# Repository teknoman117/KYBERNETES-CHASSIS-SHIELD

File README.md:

# Kybernetes 2 Chassis Control Shield

Arduino Uno R3 shield for controlling the chassis functions of Kybernetes 2

## Functions

* Battery Protection for Motion Battery
* Isolated control of Steering Servos
* Isolated control of ESC
* Kill Switch (ATTINY85) - out of band ESC arming management, Radio PWM input
* Quadrature Encoder Input for velocity control and odometry
* Bumper Input for contact sensors
* I2C bus for current sensors, sonar, imu, etc.

## Firmware

### Assembled

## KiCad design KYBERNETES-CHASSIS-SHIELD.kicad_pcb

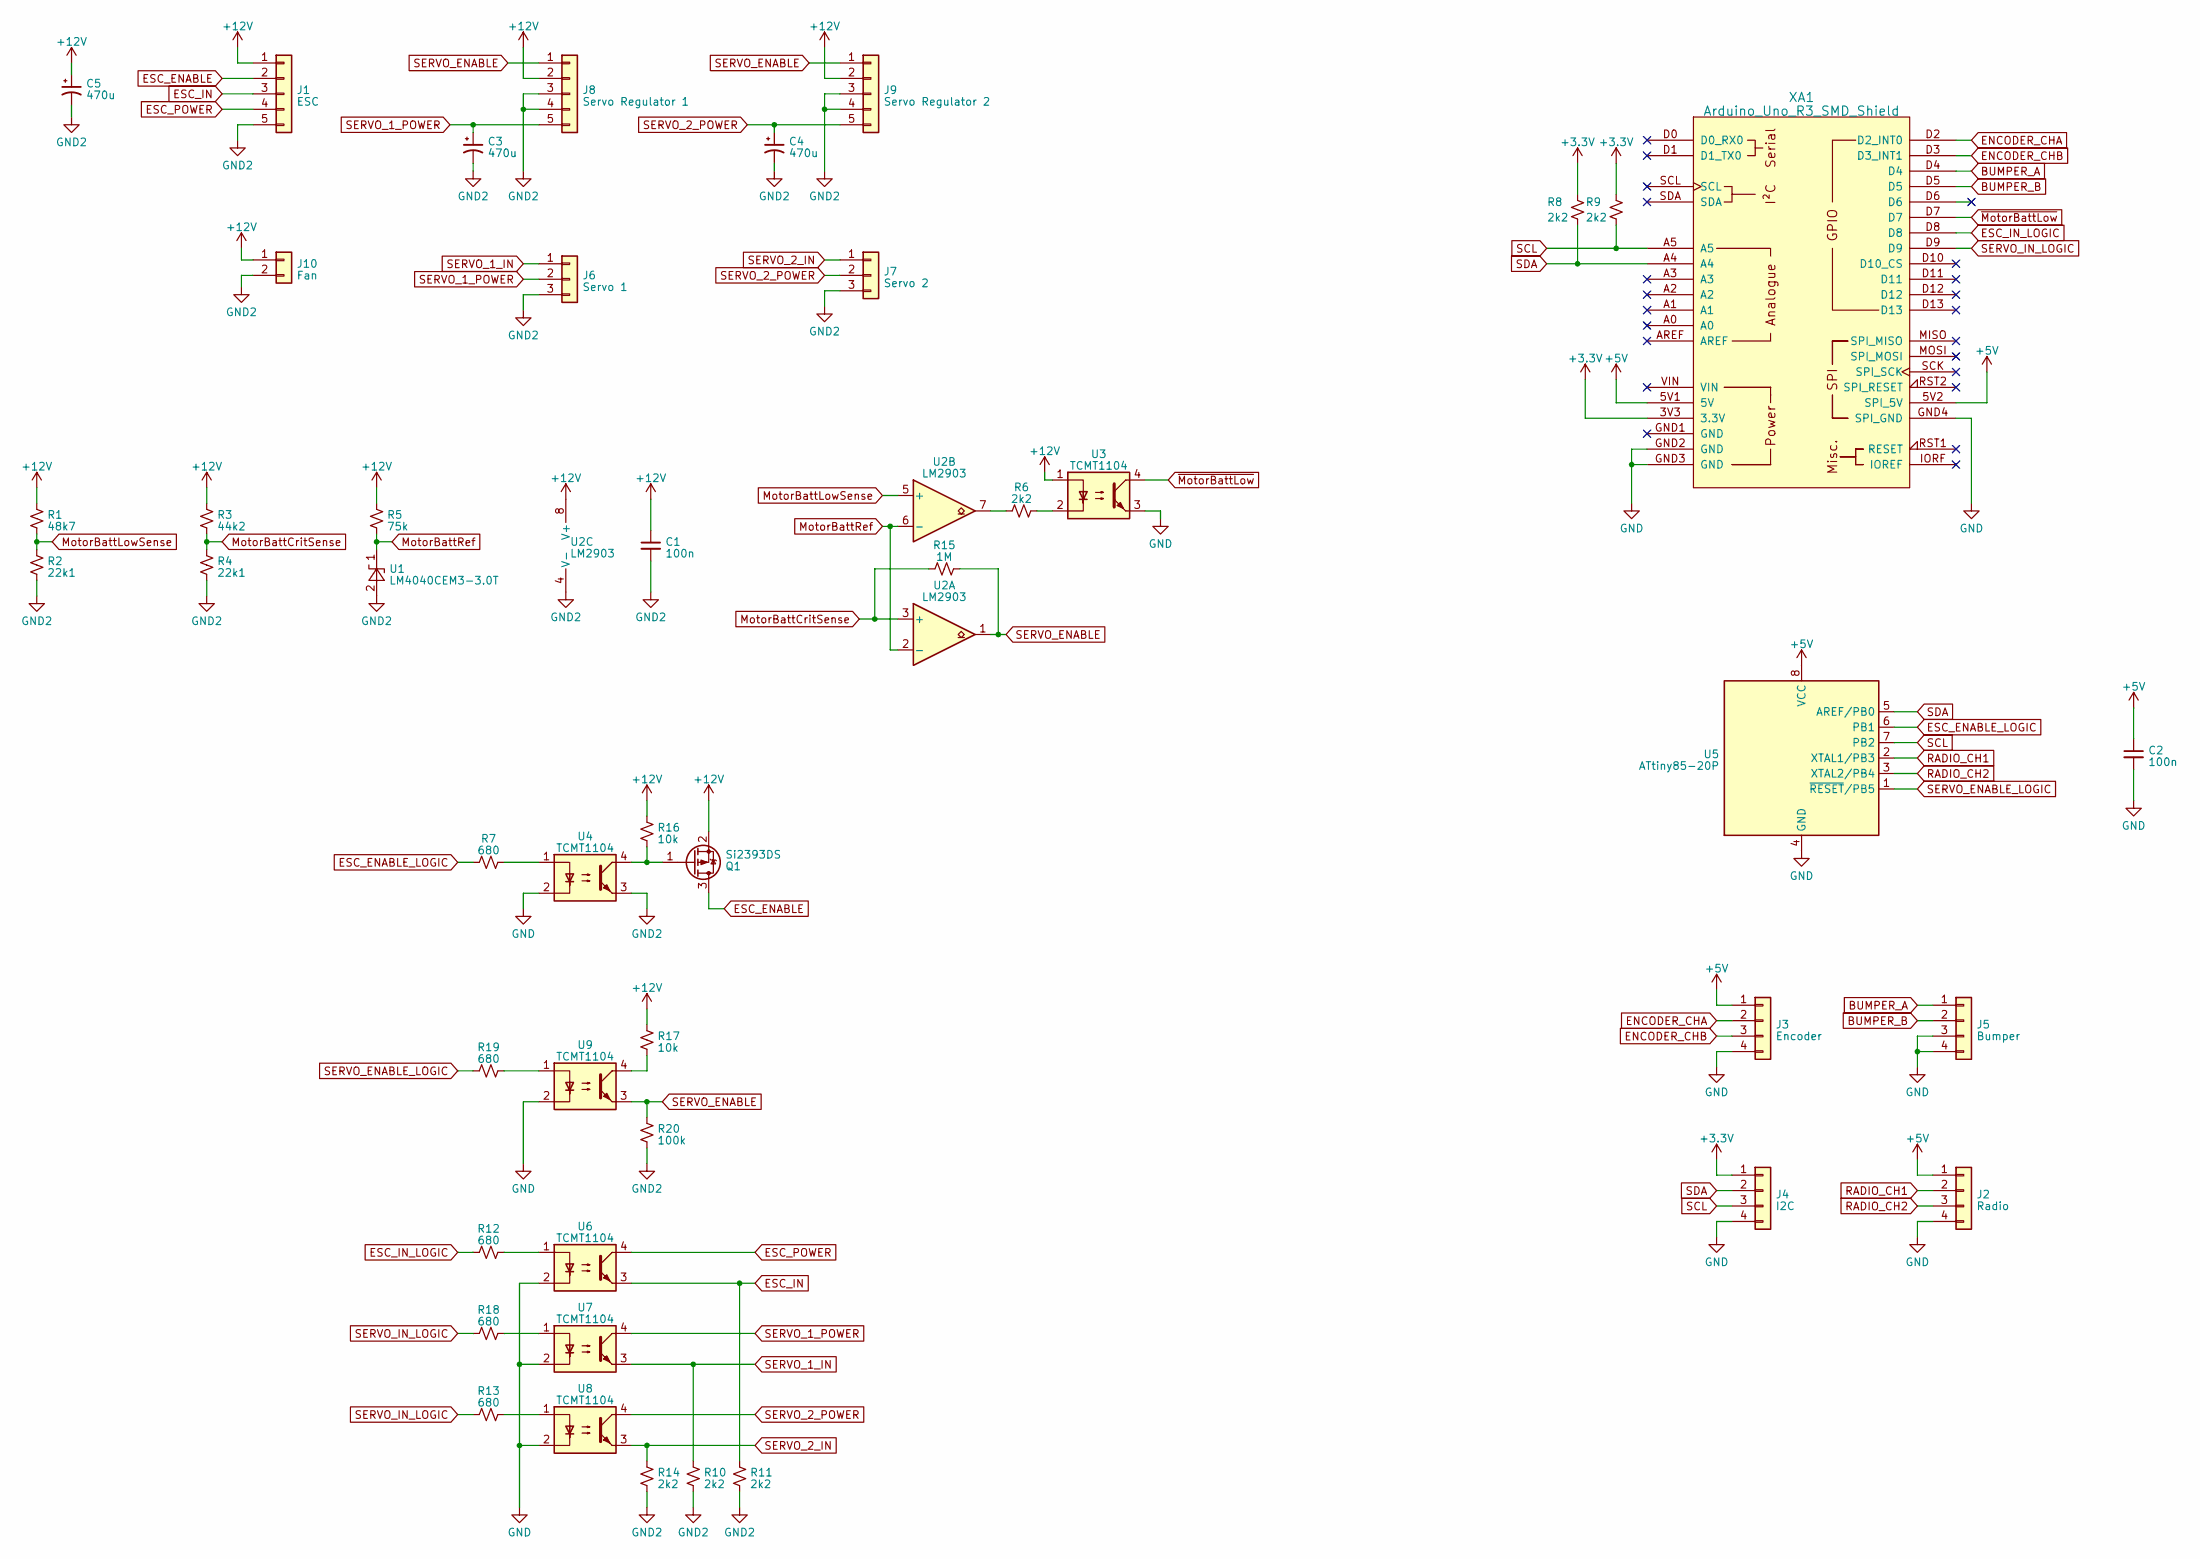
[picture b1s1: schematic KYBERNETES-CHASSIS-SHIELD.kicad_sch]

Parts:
C1, C2: 100n; C_0603_1608Metric_Pad1.08x0.95mm_HandSolder
C3, C4, C5: 470u; CP_Elec_10x10.5
J1: ESC; JST_PH_B5B-PH-K_1x05_P2.00mm_Vertical
J2: Radio; JST_PH_B4B-PH-K_1x04_P2.00mm_Vertical
J3: Encoder; JST_PH_B4B-PH-K_1x04_P2.00mm_Vertical
J4: I2C; JST_PH_B4B-PH-K_1x04_P2.00mm_Vertical
J5: Bumper; JST_PH_B4B-PH-K_1x04_P2.00mm_Vertical
J6: Servo 1; PinHeader_1x03_P2.54mm_Vertical
J7: Servo 2; PinHeader_1x03_P2.54mm_Vertical
J8: Servo Regulator 1; PinHeader_1x05_P2.54mm_Vertical
J9: Servo Regulator 2; PinHeader_1x05_P2.54mm_Vertical
J10: Fan; JST_PH_B2B-PH-K_1x02_P2.00mm_Vertical
Q1: Si2393DS; SOT-23
R1: 48k7; R_0603_1608Metric_Pad0.98x0.95mm_HandSolder
R2, R4: 22k1; R_0603_1608Metric_Pad0.98x0.95mm_HandSolder
R3: 44k2; R_0603_1608Metric_Pad0.98x0.95mm_HandSolder
R5: 75k; R_0603_1608Metric_Pad0.98x0.95mm_HandSolder
R6, R8, R9, R10, R11, R14: 2k2; R_0603_1608Metric_Pad0.98x0.95mm_HandSolder
R7, R12, R13, R18, R19: 680; R_0603_1608Metric_Pad0.98x0.95mm_HandSolder
R15: 1M; R_0603_1608Metric_Pad0.98x0.95mm_HandSolder
R16, R17: 10k; R_0603_1608Metric_Pad0.98x0.95mm_HandSolder
R20: 100k; R_0603_1608Metric_Pad0.98x0.95mm_HandSolder
U1: LM4040CEM3-3.0T; SOT-23-3
U2: LM2903; TSSOP-8_4.4x3mm_P0.65mm
U3, U4, U6, U7, U8, U9: TCMT1104; SOP-4_4.4x2.6mm_P1.27mm
U5: ATtiny85-20P; DIP-8_W7.62mm
XA1: Arduino_Uno_R3_SMD_Shield; Arduino_Uno_R3_Shield

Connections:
+3.3V: J4.1, R8.1, R9.1, XA1.3V3 (3.3V)
+5V: C2.1, J2.1, J3.1, U5.8 (VCC), XA1.5V1 (5V), XA1.5V2 (SPI_5V)
+12V: C1.1, C5.1, J1.1, J8.2, J9.2, J10.1, Q1.2 (S), R1.1, R3.1, R5.1, R16.1, R17.1, U2.8 (V+), U3.1
BUMPER_A: J5.1, XA1.D4
BUMPER_B: J5.2, XA1.D5
ENCODER_CHA: J3.2, XA1.D2 (D2_INT0)
ENCODER_CHB: J3.3, XA1.D3 (D3_INT1)
ESC_ENABLE: J1.2, Q1.3 (D)
ESC_ENABLE_LOGIC: R7.1, U5.6 (PB1)
ESC_IN: J1.3, R11.1, U6.3
ESC_IN_LOGIC: R12.1, XA1.D8
ESC_POWER: J1.4, U6.4
GND: C2.2, J2.4, J3.4, J4.4, J5.3, J5.4, U3.3, U4.2, U5.4 (GND), U6.2, U7.2, U8.2, U9.2, XA1.GND2 (GND), XA1.GND3 (GND), XA1.GND4 (SPI_GND)
GND2: C1.2, C3.2, C4.2, C5.2, J1.5, J6.3, J7.3, J8.3, J8.4, J9.3, J9.4, J10.2, R2.2, R4.2, R10.2, R11.2, R14.2, R20.2, U1.2 (A), U2.4 (V-), U4.3
MotorBattCritSense: R3.2, R4.1, R15.1, U2.3 (+)
MotorBattLowSense: R1.2, R2.1, U2.5 (+)
MotorBattRef: R5.2, U1.1 (K), U2.2 (-), U2.6 (-)
unnamed: Q1.1 (G), R16.2, U4.4
unnamed: R6.1, U2.7
unnamed: R6.2, U3.2
unnamed: R7.2, U4.1
unnamed: R12.2, U6.1
unnamed: R13.2, U8.1
unnamed: R17.2, U9.4
unnamed: R18.2, U7.1
unnamed: R19.2, U9.1
RADIO_CH1: J2.2, U5.2 (XTAL1/PB3)
RADIO_CH2: J2.3, U5.3 (XTAL2/PB4)
SCL: J4.3, R9.2, U5.7 (PB2), XA1.A5
SDA: J4.2, R8.2, U5.5 (AREF/PB0), XA1.A4
SERVO_1_IN: J6.1, R10.1, U7.3
SERVO_1_POWER: C3.1, J6.2, J8.5, U7.4
SERVO_2_IN: J7.1, R14.1, U8.3
SERVO_2_POWER: C4.1, J7.2, J9.5, U8.4
SERVO_ENABLE: J8.1, J9.1, R15.2, R20.1, U2.1, U9.3
SERVO_ENABLE_LOGIC: R19.1, U5.1 (~RESET/PB5)
SERVO_IN_LOGIC: R13.1, R18.1, XA1.D9
~MotorBattLow: U3.4, XA1.D7

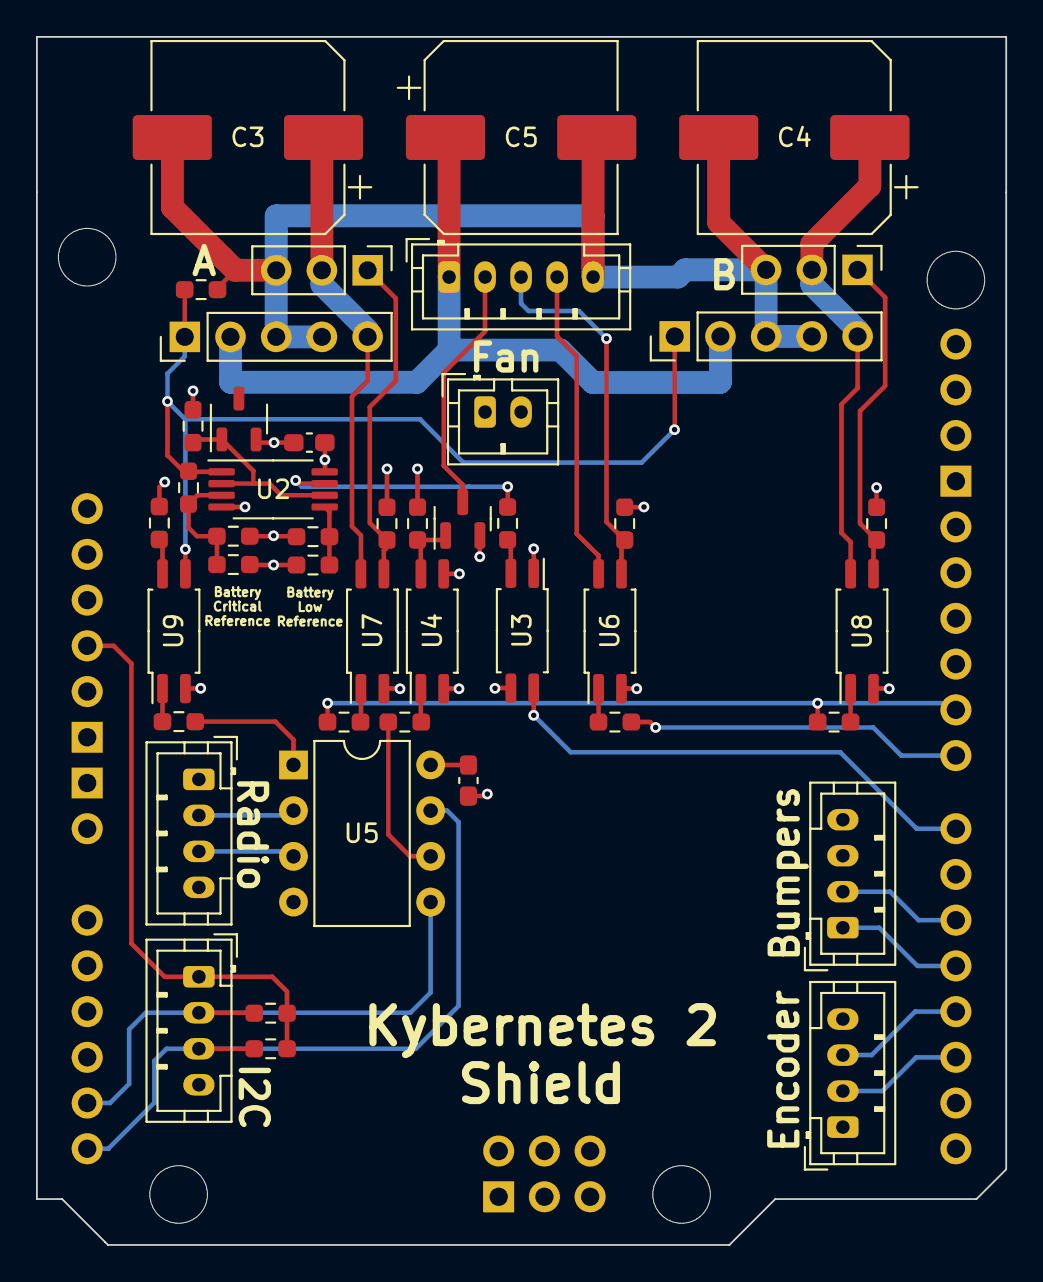
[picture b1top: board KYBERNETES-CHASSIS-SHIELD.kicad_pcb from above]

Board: 4 copper layers, 53.8 x 67.1 mm, 46 parts (0 on the bottom side), 38 nets.

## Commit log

2023-03-01 rework into 4 layer board
2023-03-01 version 1.0
2023-03-02 add comparator bias resistor, increase low voltage thresholds, add large capacitors for servos
2023-03-03 fix the incorrect footprint for desired capacitors (wurth 875115357006)
2023-03-14 add a mosfet after the esc enable opto to as it is not just an enable line as previously thought. needs more current than opto can provide.
2023-03-15 change the servo enable optoisolator to a high side switch
2024-08-16 add readme and license
2024-08-16 add images and firmware links
2024-08-16 add schematic rendering
